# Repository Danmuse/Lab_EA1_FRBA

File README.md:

<!-- Official repository: https://github.com/Danmuse/Lab_EA1_FRBA -->
<!--
<details>
  <summary><strong><span>&#160;</span>References</strong></summary>
  <ul>
    <span>&#10038;</span> [#](#).
  </ul>
</details>
-->

## 📕️ __Overview__

The **Single-stage amplifiers** project involves the design, simulation, and experimental validation of single-stage amplifier circuits using bipolar junction transistors (BJTs) and field-effect transistors (FETs). The main objective is to compare theoretical small-signal and biasing calculations with actual laboratory measurements.

### 🔌️ __Hardware & Setup__

- [x] [Identification of the sensors, modules and controllers used.](https://github.com/Danmuse/Lab_EA1_FRBA/issues/1) `3 MH`
<details>
  <summary><strong><span>&#160;</span>Electronic components</strong></summary>
  <ul>
    <span>&#10038;</span> <b>SMAJ12A</b>: TVS Diodes for input overvoltage protection.<br>
    <span>&#10038;</span> <b>RV1 - RV12</b>: 100kΩ Potentiometers for bias and load adjustment.<br>
    <span>&#10038;</span> <b>C1 - C9</b>: 1µF Coupling and bypass capacitors (Optional).<br>
    <span>&#10038;</span> <b>JP1 - JP12</b>: Solder jumpers for circuit configuration.<br>
    <span>&#10038;</span> <b>J11, J24, J37</b>: 3-pin headers for BJT/FET transistor swapping.<br>
    <span>&#10038;</span> <b>J13, J26, J39</b>: BNC/SMA Connectors for signal output (COLLECTOR, EMITTER, BASE).<br>
    <span>&#10038;</span> <b>Screw Terminals</b>: Input connectors for power supply (VCC/GND) and signal source.<br>
  </ul>
</details>

- [x] [Hardware installations and cabinet design.](https://github.com/Danmuse/Lab_EA1_FRBA/issues/2) `20 MH`
- [x] [Development board (Schematic and PCB).](https://github.com/Danmuse/Lab_EA1_FRBA/issues/3) `16 MH`
- [ ] [Circuit simulations with LTSpice.](https://github.com/Danmuse/Lab_EA1_FRBA/issues/4) `0 MH`

### 📚️ __Documentation & Doxygen__

- [ ] [Comprehensive and extensive project report.](https://github.com/Danmuse/Lab_EA1_FRBA/issues/5) `0 MH`
- [ ] [Illustrations of the experience and trials.](https://github.com/Danmuse/Lab_EA1_FRBA/issues/6) `0 MH`
- [ ] [Load component datasheet.](https://github.com/Danmuse/Lab_EA1_FRBA/issues/7) `0 MH`

---

> [!TIP]
> This section showcases the transition from theoretical design to physical implementation.

<div align="center">
  <table>
    <tr>
      <td align="center"><b>Schematic circuit</b></td>
      <td align="center"><b>PCB (TOP view)</b></td>
      <td align="center"><b>PCB (BOTTOM view) + Layout</b></td>
    </tr>
    <tr>
      <td></td>
      <td></td>
      <td></td>
    </tr>
  </table>
</div>

<!-- 

<details>
  <summary><strong><span>&#160;</span>Oscilloscope Measurements</strong></summary>
  <br>
  <p align="center">
    
    <br>
    <i>Experimental verification of voltage gain ($|A_{vs}|$) and signal phase.</i>
  </p>
</details>

---

## 🌟️ __Contributing__

General Hardware Developer: __@Danmuse__  
Documentation Manager Editor: __@Danmuse__   

<br>

 -->

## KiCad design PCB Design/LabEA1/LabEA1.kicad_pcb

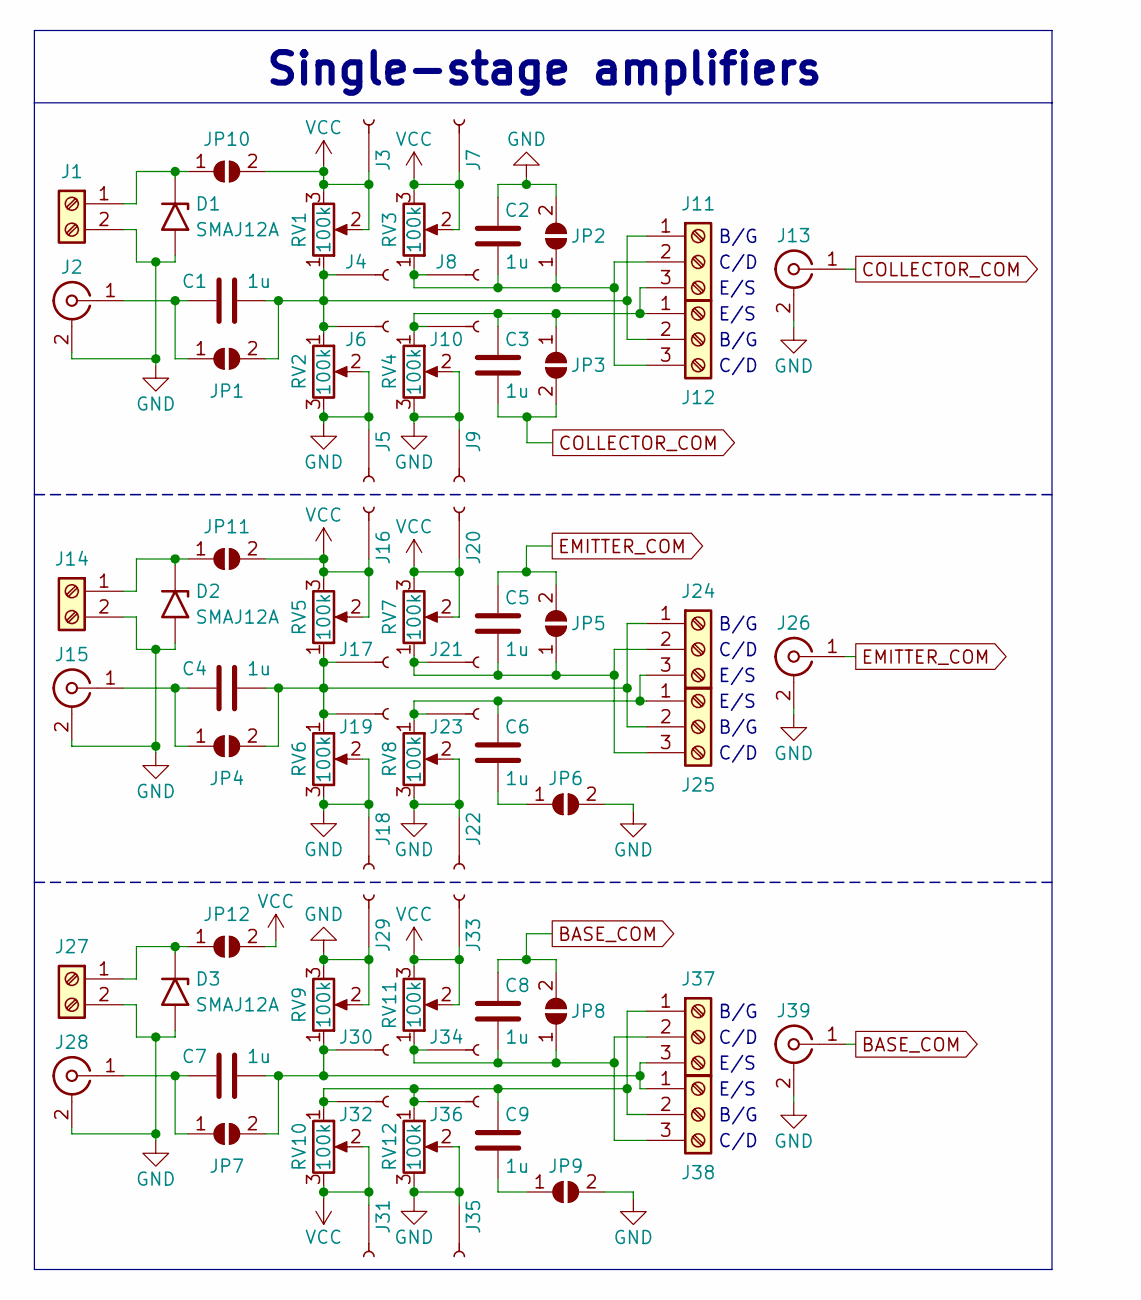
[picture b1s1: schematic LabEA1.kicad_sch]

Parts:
C1, C2, C3, C4, C5, C6, C7, C8, C9: 1u; C_Rect_L7.0mm_W2.5mm_P5.00mm
D1, D2, D3: SMAJ12A; D_SMA
J1, J14, J27: Screw_Terminal_01x02; 1725656
J2, J13, J15, J26, J28, J39: Conn_Coaxial; BNC_Amphenol_B6252HB-NPP3G-50_Horizontal
J3, J4, J5, J6, J7, J8, J9, J10, J16, J17, J18, J19, J20, J21, J22, J23, J29, J30, J31, J32, J33, J34, J35, J36: Conn_01x01_Socket; 5006
J11, J12, J24, J25, J37, J38: Screw_Terminal_01x03; 1725669
JP1, JP2, JP3, JP4, JP5, JP6, JP7, JP8, JP9, JP10, JP11, JP12: SolderJumper_2_Open; PinHeader_1x02_P2.54mm_Vertical
RV1, RV2, RV3, RV4, RV5, RV6, RV7, RV8, RV9, RV10, RV11, RV12: 100k; Potentiometer_Bourns_3296W_Vertical

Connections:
BASE_COM: C8.2, J39.1 (In), JP8.2 (B)
COLLECTOR_COM: C3.2, J13.1 (In), JP3.2 (B)
EMITTER_COM: C5.2, J26.1 (In), JP5.2 (B)
GND: C2.2, D1.2 (A2), D2.2 (A2), D3.2 (A2), J1.2, J2.2 (Ext), J5.1, J9.1, J13.2 (Ext), J14.2, J15.2 (Ext), J18.1, J22.1, J26.2 (Ext), J27.2, J28.2 (Ext), J29.1, J35.1, J39.2 (Ext), JP2.2 (B), JP6.2 (B), JP9.2 (B), RV2.2, RV2.3, RV4.2, RV4.3, RV6.2, RV6.3, RV8.2, RV8.3, RV9.2, RV9.3, RV12.2, RV12.3
unnamed: D1.1 (A1), J1.1, JP10.1 (A)
unnamed: D2.1 (A1), J14.1, JP11.1 (A)
unnamed: D3.1 (A1), J27.1, JP12.1 (A)
unnamed: C1.1, J2.1 (In), JP1.1 (A)
unnamed: C3.1, J10.1, J11.3, J12.1, JP3.1 (A), RV4.1
unnamed: C1.2, J4.1, J6.1, J11.1, J12.2, JP1.2 (B), RV1.1, RV2.1
unnamed: C2.1, J8.1, J11.2, J12.3, JP2.1 (A), RV3.1
unnamed: C4.1, J15.1 (In), JP4.1 (A)
unnamed: C4.2, J17.1, J19.1, J24.1, J25.2, JP4.2 (B), RV5.1, RV6.1
unnamed: C5.1, J21.1, J24.2, J25.3, JP5.1 (A), RV7.1
unnamed: C6.1, J23.1, J24.3, J25.1, RV8.1
unnamed: C7.1, J28.1 (In), JP7.1 (A)
unnamed: C7.2, J30.1, J37.3, J38.1, JP7.2 (B), RV9.1
unnamed: C9.1, J32.1, J36.1, J37.1, J38.2, RV10.1, RV12.1
unnamed: C8.1, J34.1, J37.2, J38.3, JP8.1 (A), RV11.1
unnamed: C6.2, JP6.1 (A)
unnamed: C9.2, JP9.1 (A)
VCC: J3.1, J7.1, J16.1, J20.1, J31.1, J33.1, JP10.2 (B), JP11.2 (B), JP12.2 (B), RV1.2, RV1.3, RV3.2, RV3.3, RV5.2, RV5.3, RV7.2, RV7.3, RV10.2, RV10.3, RV11.2, RV11.3

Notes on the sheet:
B/G
C/D
E/S
C/D
E/S
----------------------------------------------------------------
----------------------------------------------------------------
Single-stage amplifiers

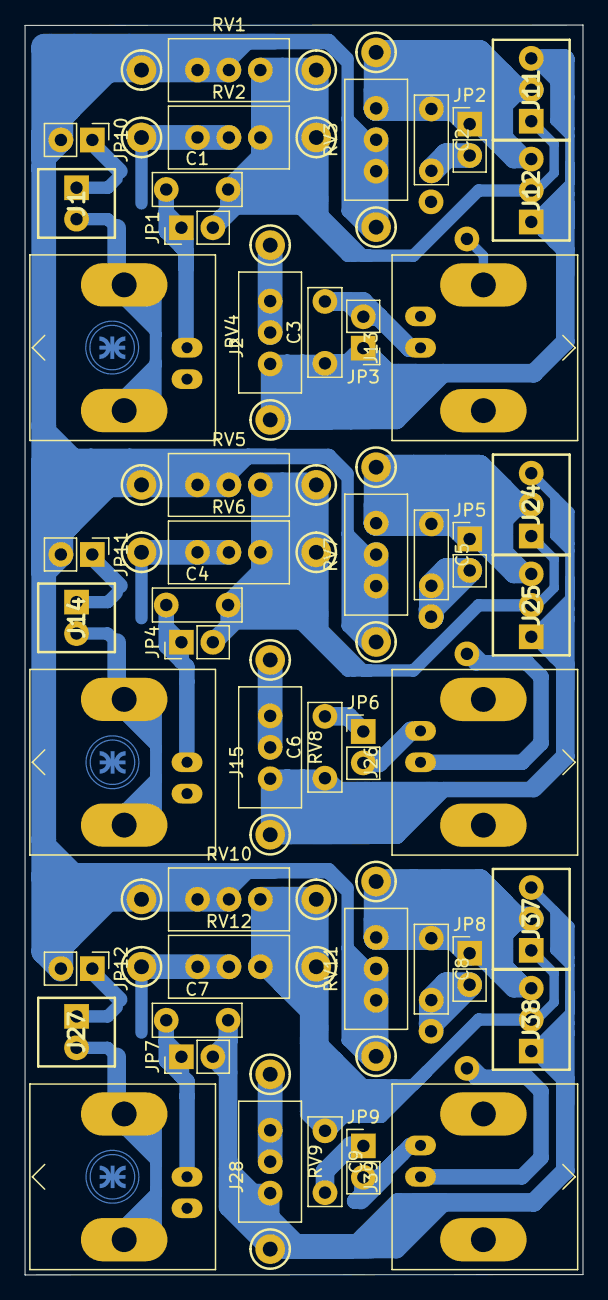
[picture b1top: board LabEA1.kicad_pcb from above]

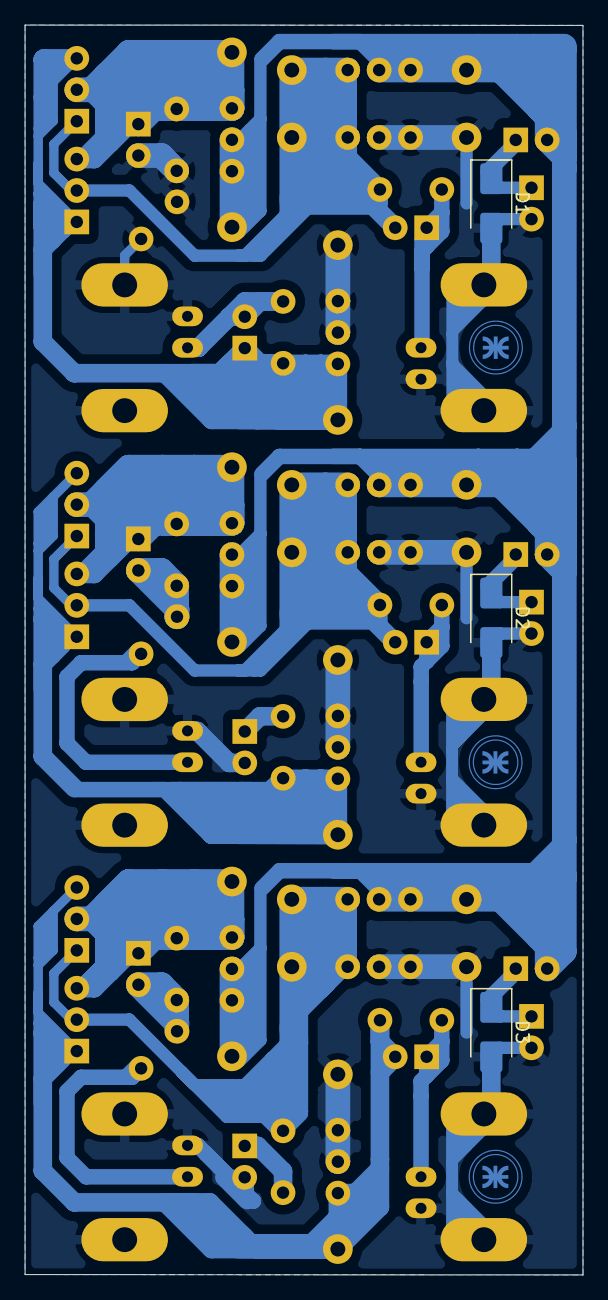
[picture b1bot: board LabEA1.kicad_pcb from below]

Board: 2 copper layers, 45.1 x 101.0 mm, 75 parts (3 on the bottom side), 22 nets.

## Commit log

2026-04-13 Complete schematic circuit and PCB design ~ Issue related #3
2026-05-02 Include images and update the README file ~ Issue related #1, #2 and #6
